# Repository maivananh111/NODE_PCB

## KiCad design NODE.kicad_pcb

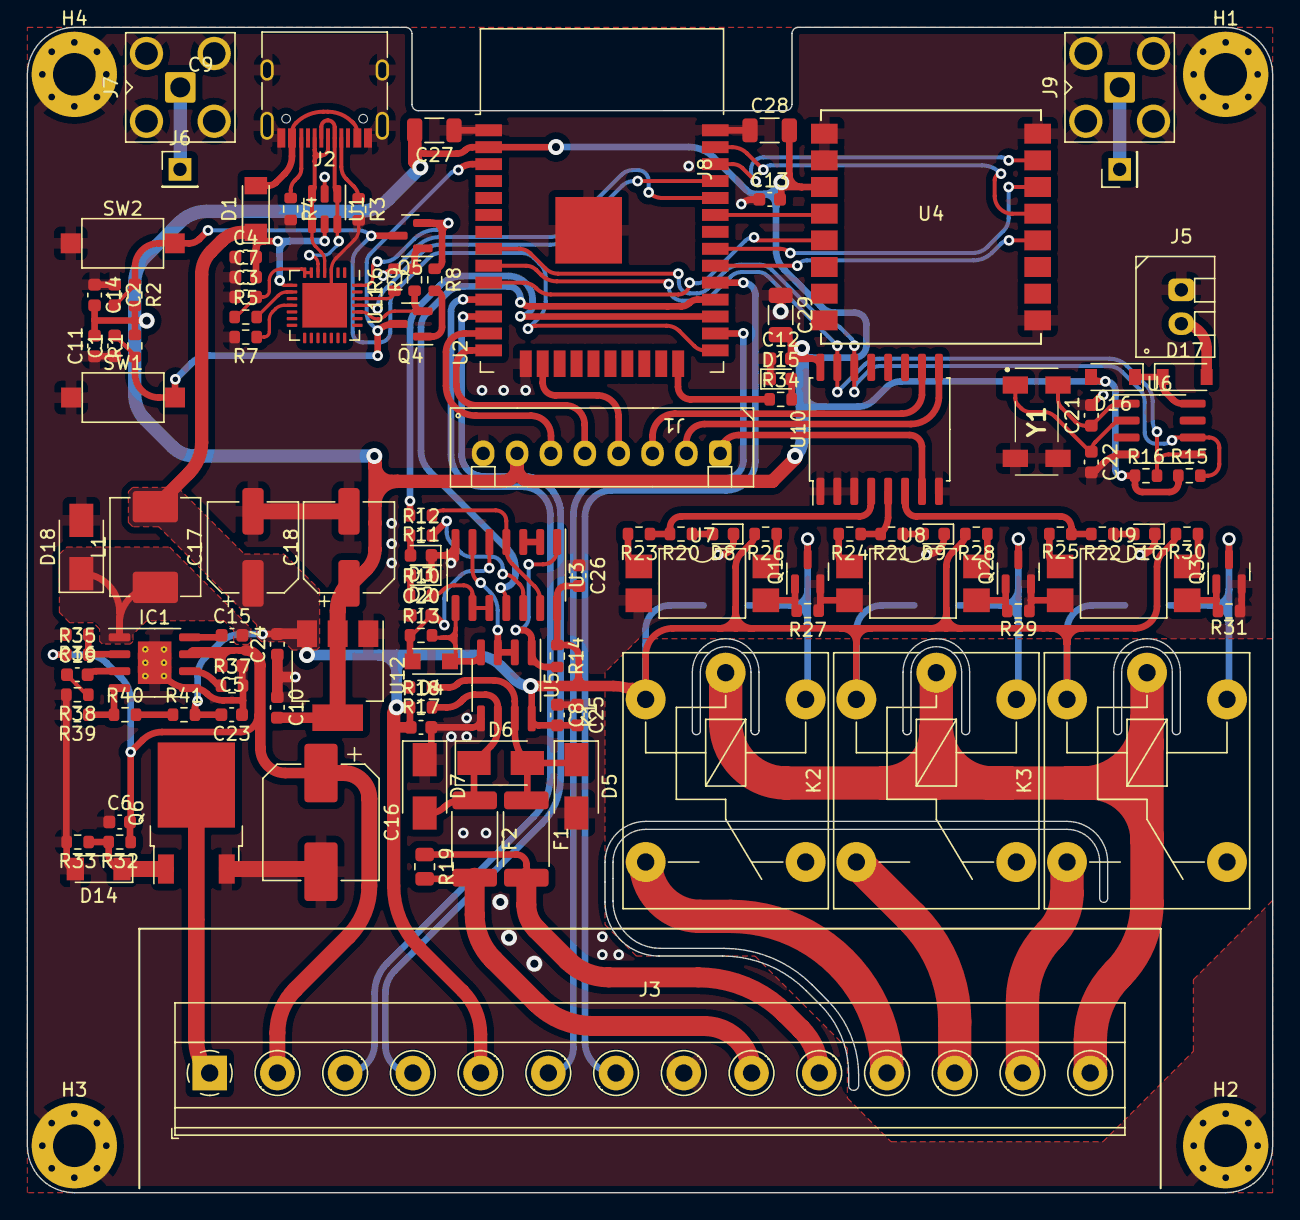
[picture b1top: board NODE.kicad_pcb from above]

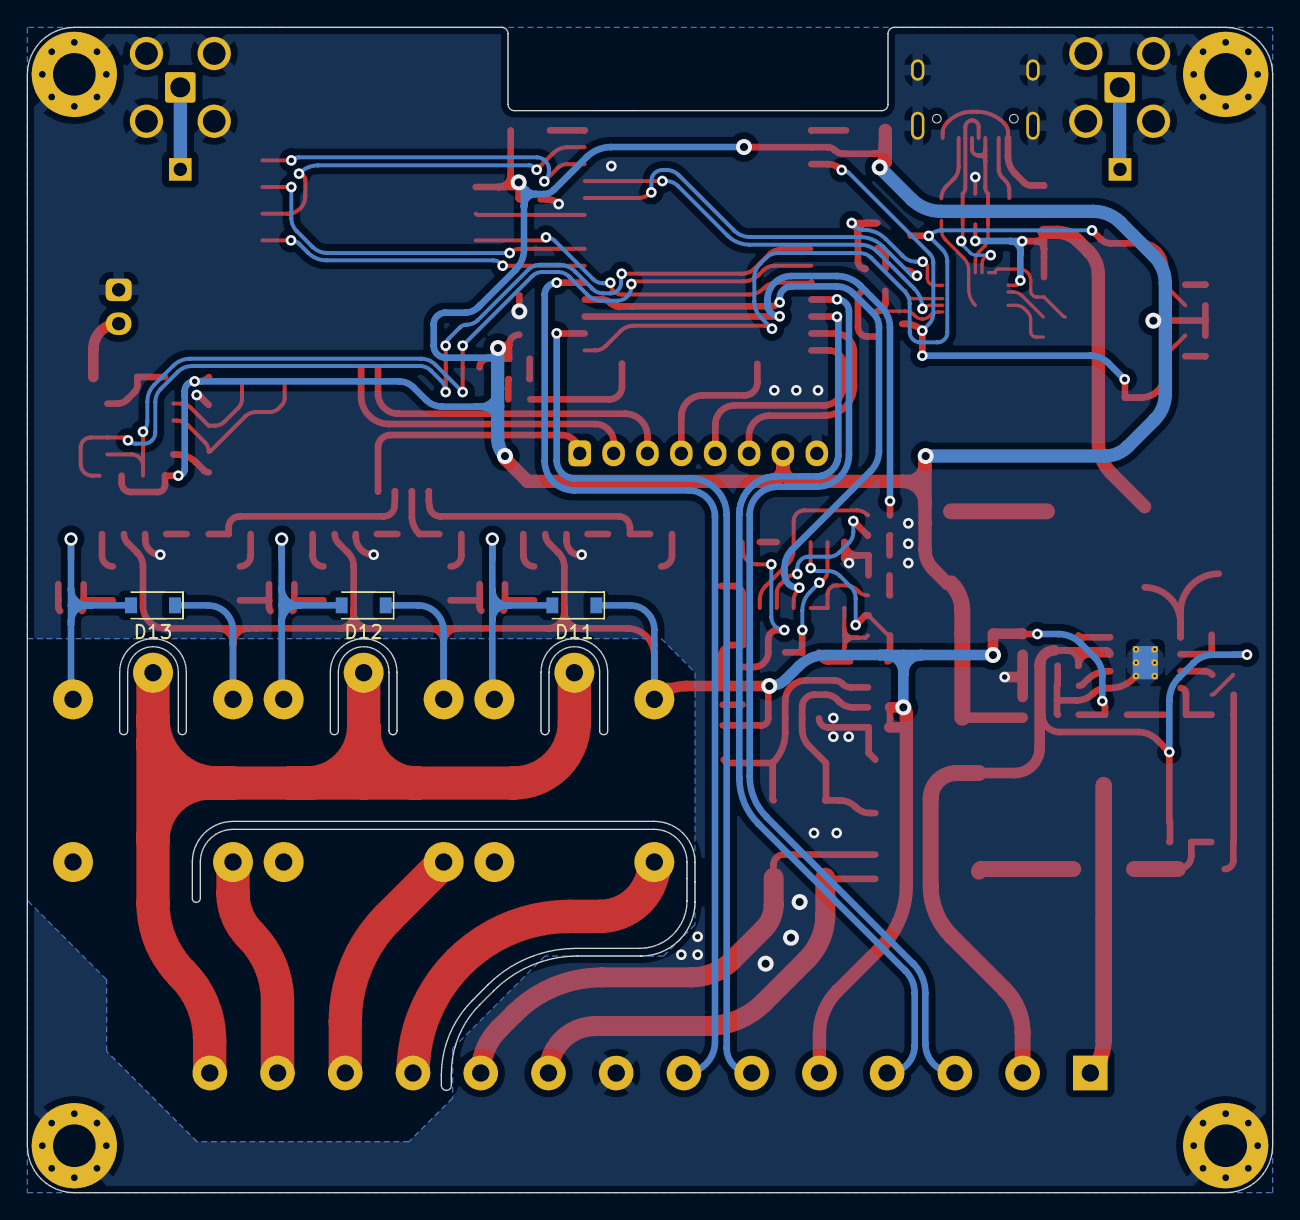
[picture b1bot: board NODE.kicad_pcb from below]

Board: 2 copper layers, 93.4 x 87.4 mm, 128 parts (3 on the bottom side), 95 nets.

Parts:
C1, C2, C3, C4, C5, C6, C7, C8, C9, C10, C11, C12, C13, C14, C15, C23, C24, C25, C26: 100nF; C_0603_1608Metric
C16: 220uF; CP_Elec_8x10.5
C17, C18: 220uF; CP_Elec_6.3x7.7
C19: 220pF; C_0603_1608Metric
C20, C21, C22: 22pF; C_0603_1608Metric
C27, C28, C29: 10uF; C_1206_3216Metric
D1, D14: BZV55B18; D_MiniMELF
D2: TxLED; LED_0603_1608Metric
D3: RxLED; LED_0603_1608Metric
D4: 1N4007; Nexperia_CFP3_SOD-123W
D5, D6, D7: D_TVS; D_SMA
D8, D9, D10: LED; LED_0603_1608Metric
D11, D12, D13: 1N4007; D_SOD-123
D15: RUN; LED_0603_1608Metric
D16, D17: 1N5819; D_SOD-123
D18: SS34; D_SMA
F1: Fuse1; Fuse_2512_6332Metric
F2: Fuse2; Fuse_2512_6332Metric
H1: H1; MountingHole_3.2mm_M3_Pad_Via
H2: H2; MountingHole_3.2mm_M3_Pad_Via
H3: H3; MountingHole_3.2mm_M3_Pad_Via
H4: H4; MountingHole_3.2mm_M3_Pad_Via
IC1: MP1584EN; SOIC-8-1EP_3.9x4.9mm_P1.27mm_EP2.514x3.2mm_ThermalVias
J1: CTRL_CONNECTOR; XH_8P_2.54mm_Vertical
J2: USB_C_Receptacle_USB2.0; USB_C_Receptacle_HRO_TYPE-C-31-M-12
J3: CONNECTOR; TerminalBlock_Phoenix_MKDS-1,5-14-5.08_1x14_P5.08mm_Horizon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
J5: BATT; XH_2P_2.54mm_Vertical
J6: ESP_ANT; PinHeader_1x01_P2.54mm_Vertical
J7, J9: Conn_Coaxial; SMA_Amphenol_901-143_Horizontal
J8: LORA_ANT; PinHeader_1x01_P2.54mm_Vertical
K1, K2, K3: FINDER-36.11; Relay_SPDT_Finder_36.11
L1: 10uH; L_Abracon_ASPI-0630LR
Q1, Q2, Q3, Q4, Q5: BC847; SOT-23
Q6: QM6006D; TO-252-2
R1, R2, R5, R7, R8, R9, R27, R29, R31, R33, R36: 10k; R_0603_1608Metric
R3, R4: 5k6; R_0603_1608Metric
R6, R32, R34: 100; R_0603_1608Metric
R10, R11, R12, R20, R21, R22, R23, R24, R25: 220; R_0603_1608Metric
R13, R38: 68k; R_0603_1608Metric
R14, R15, R16, R17, R18, R26, R28, R30, R41: 4k7; R_0603_1608Metric
R19: 120/2W; R_0805_2012Metric
R35: 47k; R_0603_1608Metric
R37, R40: 200k; R_0603_1608Metric
R39: 39k; R_0603_1608Metric
SW1: Reset; SW_SPST_CK_RS282G05A3
SW2: Boot; SW_SPST_CK_RS282G05A3
U1: USBLC6-2SC6; SOT-23-6
U2: ESP32-WROOM-32
U3: 74HC14; SOIC-14_3.9x8.7mm_P1.27mm
U4: Ra-02; Ai-Thinker-Ra-01-LoRa
U5: MAX485E; SOIC-8_3.9x4.9mm_P1.27mm
U6: PCF8563T; SOIC-8_3.9x4.9mm_P1.27mm
U7, U8, U9: LTV-817S; SMDIP-4_W9.53mm
U10: PCF8574A; SOIC-16W_7.5x10.3mm_P1.27mm
U11: CP2102N-Axx-xQFN28; QFN-28-1EP_5x5mm_P0.5mm_EP3.35x3.35mm
U12: AP1117-33; SOT-223-3_TabPin2
Y1: 32.7680KHz; MC306327680KE3ROHS

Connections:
+3.3V: C10.2, C11.2, C12.2, C13.2, C14.2, C18.1, C27.2, C28.2, C29.2, D16.2 (A), J1.7, R1.2, R2.2, R15.1, R16.1, U2.2 (VDD), U4.3 (VDD), U10.16 (VDD), U12.2 (VO)
+5V: C4.2, C7.2, C8.2, C9.2, C17.1, C23.2, C24.2, C25.2, C26.2, D1.1 (K), D11.1 (K), D12.1 (K), D13.1 (K), J3.5, K1.A1, K2.A1, K3.A1, L1.2, R14.1, R18.1, R26.2, R28.2, R30.2, R41.2, U1.5 (VBUS), U3.14 (VCC), U5.8 (VCC), U11.8 (VBUS), U12.3 (VI)
A+: F1.2, J3.10, R19.1
B-: F2.2, J3.9, R19.2
BUTTON1: J1.6, U2.13 (IO14)
BUTTON2: J1.5, U2.14 (IO12)
BUTTON3: J1.4, U2.16 (IO13)
Boot: C2.2, Q5.3 (C), R2.1, SW2.2, U2.25 (IO0)
COM: J3.14, K1.11, K2.11, K3.11
GND: C1.1, C2.1, C3.1, C4.1, C5.1, C6.1, C7.1, C8.1, C9.1, C10.1, C11.1, C12.1, C13.1, C14.1, C16.2, C17.2, C18.2, C20.1, C21.2, C22.2, C23.1, C24.1, C25.1, C26.1, C27.1, C28.1, C29.1, D2.1 (K), D3.1 (K), D5.2 (A2), D7.1 (A1), D8.1 (K), D9.1 (K), D10.1 (K), D14.2 (A), D15.1 (K), D18.2 (A), H1.1, H2.1, H3.1, H4.1, IC1.5 (GND), IC1.9 (EP), J1.8, J2.A1 (GND), J2.A12 (GND), J2.B1 (GND), J2.B12 (GND), J2.S1 (SHIELD), J3.8, J5.1, J7.2 (Ext), J9.2 (Ext), Q1.2 (E), Q2.2 (E), Q3.2 (E), Q6.3 (S), R3.2, R4.2, R7.2, R17.2, R27.1, R29.1, R31.1, R33.2, R36.2, R37.2, R38.2, R39.2, SW1.1, SW2.1, U1.2 (GND), U2.1 (GND), U2.15 (GND), U2.38 (GND), U2.39 (GND), U3.7 (GND), U4.1 (GND), U4.2 (GND), U4.9 (GND), U4.16 (GND), U5.5 (GND), U6.4 (VSS), U7.2, U8.2, U9.2, U10.1 (A0), U10.2 (A1), U10.3 (A2), U10.8 (VSS), U11.3 (GND), U11.29 (GND), U12.1 (GND), Y1.2 (GND_1), Y1.3 (GND_2)
GNDPWR: J3.1, Q6.2 (D)
I2C_SCL: J3.6, U2.26 (IO4)
I2C_SDA: J3.7, U2.29 (IO5)
IO0: J3.3, U2.11 (IO26)
IO1: J3.4, U2.12 (IO27)
LED1: J1.1, U10.7 (P3)
LED2: J1.2, U10.9 (P4)
LED3: J1.3, U10.10 (P5)
Lora_CS: U2.36 (IO22), U4.15 (~NSS)
Lora_INT: U2.10 (IO25), U4.5 (DIO0)
Lora_MISO: U2.37 (IO23), U4.13 (MISO)
Lora_MOSI: U2.31 (IO19), U4.14 (MOSI)
Lora_RST: U2.33 (IO21), U4.4 (~RESET)
Lora_SCK: U2.30 (IO18), U4.12 (SCK)
NO1: J3.11, K1.14
NO2: J3.12, K2.14
NO3: J3.13, K3.14
unnamed: C3.2, R5.1, U11.6 (VDD), U11.7 (VREGIN)
unnamed: C15.1, IC1.8 (BST)
unnamed: C15.2, D18.1 (K), IC1.1 (SW), L1.1
unnamed: C19.1, R38.1
unnamed: C19.2, IC1.3 (COMP)
unnamed: C20.2, D4.2 (A), R13.1, U3.5
unnamed: C21.1, U6.1 (OSCI), Y1.4 (CRY_2)
unnamed: C22.1, U6.2 (OSCO), Y1.1 (CRY_1)
unnamed: D1.2 (A), J2.A4 (VBUS), J2.A9 (VBUS), J2.B4 (VBUS), J2.B9 (VBUS)
unnamed: D2.2 (A), R10.1
unnamed: D3.2 (A), R12.1
unnamed: D4.1 (K), R13.2, U3.8, U5.4 (DI)
unnamed: D5.1 (A1), D6.2 (A2), F1.1, R17.1, U5.7 (B)
unnamed: D6.1 (A1), D7.2 (A2), F2.1, R18.2, U5.6 (A)
unnamed: D8.2 (A), R20.1
unnamed: D9.2 (A), R21.1
unnamed: D10.2 (A), R22.1
unnamed: D11.2 (A), K1.A2, Q1.3 (C)
unnamed: D12.2 (A), K2.A2, Q2.3 (C)
unnamed: D13.2 (A), K3.A2, Q3.3 (C)
unnamed: D14.1 (K), Q6.1 (G), R32.2, R33.1
unnamed: D15.2 (A), R34.2
unnamed: D16.1 (K), D17.1 (K), U6.8 (VDD)
unnamed: D17.2 (A), J5.2
unnamed: IC1.2 (EN), R35.2, R36.1
unnamed: IC1.4 (FB), R39.1, R40.1
unnamed: IC1.6 (FREQ), R37.1
unnamed: J2.A5 (CC1), R3.1
unnamed: J2.A6 (D+), J2.B6 (D+), U1.3 (I/O2), U1.4 (I/O2), U11.4 (D+)
unnamed: J2.A7 (D-), J2.B7 (D-), U1.1 (I/O1), U1.6 (I/O1), U11.5 (D-)
unnamed: J2.B5 (CC2), R4.1
unnamed: J6.1, J7.1 (In)
unnamed: J8.1, J9.1 (In)
unnamed: Q1.1 (B), R27.2, U7.3
unnamed: Q2.1 (B), R29.2, U8.3
unnamed: Q3.1 (B), R31.2, U9.3
unnamed: Q4.1 (B), R8.2
unnamed: Q4.2 (E), R9.1, U11.24 (~RTS)
unnamed: Q5.1 (B), R9.2
unnamed: Q5.2 (E), R8.1, U11.28 (~DTR)
unnamed: R5.2, U11.9 (~RST)
unnamed: R6.1, U11.26 (TXD)
unnamed: R7.1, U11.11 (~SUSPEND)
unnamed: R10.2, U3.9, U3.10
unnamed: R11.1, U3.4, U3.13
unnamed: R12.2, U3.12
unnamed: R14.2, U3.1, U5.1 (RO)
unnamed: R23.2, U7.1
unnamed: R24.2, U8.1
unnamed: R25.2, U9.1
unnamed: R26.1, U7.4
unnamed: R28.1, U8.4
unnamed: R30.1, U9.4
unnamed: R34.1, U2.24 (IO2)
unnamed: R40.2, R41.1
unnamed: U3.2, U3.3
unnamed: U3.6, U5.2 (~RE), U5.3 (DE)
RELAY1: R20.2, R23.1, U10.4 (P0)
RELAY2: R21.2, R24.1, U10.5 (P1)
RELAY3: R22.2, R25.1, U10.6 (P2)
RS485_Rx: R11.2, U2.27 (IO16)
RS485_Tx: U2.28 (IO17), U3.11
Reset: C1.2, Q4.3 (C), R1.1, SW1.2, U2.3 (EN)
RxD: R6.2, U2.34 (RXD0/IO3)
SCL: R15.2, U2.8 (IO32), U6.6 (SCL), U10.14 (SCL)
SDA: R16.2, U2.9 (IO33), U6.5 (SDA), U10.15 (SDA)
TxD: U2.35 (TXD0/IO1), U11.25 (RXD)
VCC: C5.2, C6.2, C16.1, IC1.7 (VIN), J3.2, R32.1, R35.1
